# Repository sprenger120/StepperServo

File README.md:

# Stepper Servo

Steering the car with the might of stepper motors

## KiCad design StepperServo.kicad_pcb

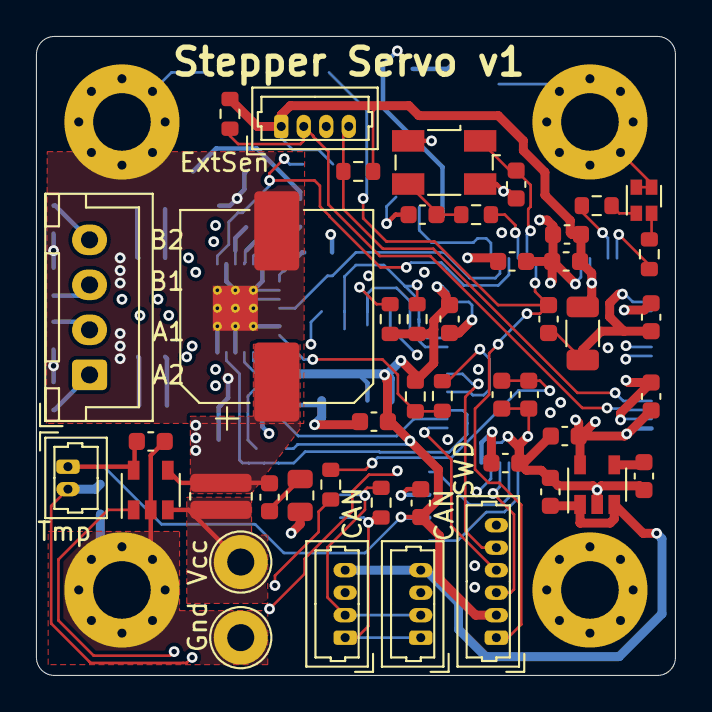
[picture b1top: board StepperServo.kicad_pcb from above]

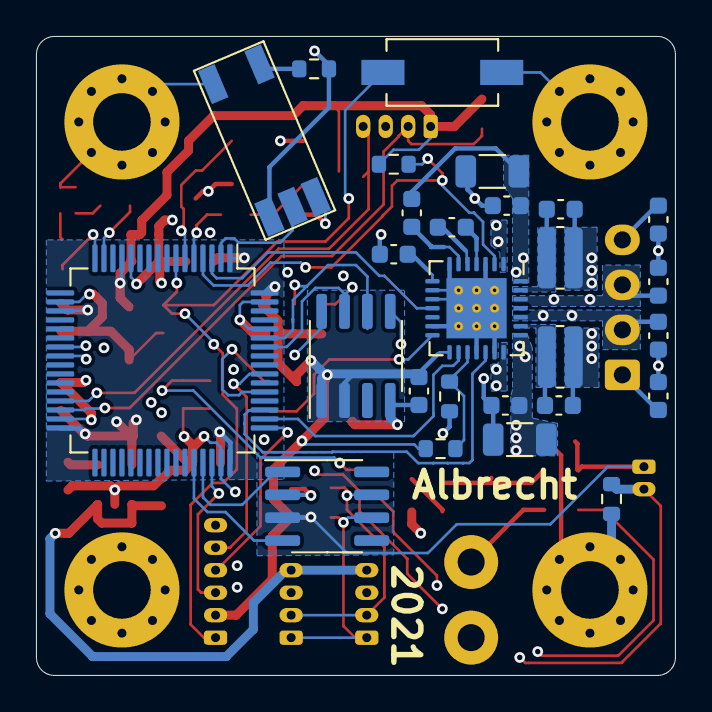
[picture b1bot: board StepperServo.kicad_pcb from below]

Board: 4 copper layers, 35.5 x 35.5 mm, 77 parts (27 on the bottom side), 48 nets.

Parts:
C1, C7, C8, C12, C13, C14, C18, C21, C23, C24, C25, C26, C27, C35, C39, C40, C41: 100nF 35V; C_0603_1608Metric
C2, C4, C9, C28: 1uF 35V; C_0603_1608Metric
C3, C17, C19, C20, C22: 470pF 100V; C_0603_1608Metric
C5, C10, C11: 10uF 35V; C_1206_3216Metric
C6: 330uF 35V; CP_Elec_10x10.5
C15: 22nF 50V; C_0603_1608Metric
C16: 2.2uF 16V; C_0603_1608Metric
C30: 10nF; C_0603_1608Metric
C33, C34: 15pF; C_0603_1608Metric
D1: LTST-C195TGKRKT; LED_LiteOn_LTST-C195TGKRKT
H1, H2, H3, H4: MountingHole_Pad; MountingHole_3.2mm_M3_Pad_Via
J1, J2: Conn_01x01_Female; TestPoint_Loop_D2.54mm_Drill1.5mm_Beaded
J3: Conn_01x04_Male; JST_XH_B4B-XH-A_1x04_P2.50mm_Vertical
J4: I2C_External; Molex_PicoBlade_53047-0410_1x04_P1.25mm_Vertical
J6: Conn_TempMotor; Molex_PicoBlade_53047-0210_1x02_P1.25mm_Vertical
J_CAN1, J_CAN2: Molex PicoBlade 4Pin; Molex_PicoBlade_53047-0410_1x04_P1.25mm_Vertical
J_SWD1: Molex PicoBlade 6Pin; Molex_PicoBlade_53047-0610_1x06_P1.25mm_Vertical
OPT1: SX3340; Omron_SX_3340
R1: 0.11; R_0612_1632Metric
R2: 120; R_0603_1608Metric
R3: 1.1R 0.5W; R_0805_2012Metric
R4: 1k; R_0603_1608Metric
R5, R7: 22k; R_0603_1608Metric
R6: 4.7k; R_0603_1608Metric
R9, R10: 270m; R_0612_1632Metric
R11, R20, R23: 10k; R_0603_1608Metric
R12, R13: 4k7; R_0603_1608Metric
R14, R15: 2k; R_0603_1608Metric
R16, R22: 220; R_0603_1608Metric
R19: 100; R_0603_1608Metric
R21: 380; R_0603_1608Metric
SW4: SW_Reset; SW_SPST_PTS636_SM25F
U1: TC1185; SOT-23-5
U2: SN65HVD232; SOIC-8_3.9x4.9mm_P1.27mm
U3: TMC2209-LA; QFN-28-1EP_5x5mm_P0.5mm_EP3.35x3.35mm_ThermalVias
U5: STM32F103RETx; LQFP-64_10x10mm_P0.5mm
U6: AS5600; SOIC-8_3.9x4.9mm_P1.27mm
U7: INA180A1; SOT-23-5
Y1: ABM3B-16MHz; Crystal_SMD_Abracon_ABM3B-4Pin_5.0x3.2mm

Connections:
+3V3: C1.1, C4.1, C5.2, C8.1, C23.2, C24.2, C25.2, C26.2, C27.2, C28.1, C30.1, C39.1, C41.1, J4.1, J6.1, J_SWD1.2, R5.1, R6.2, R7.1, R12.2, R13.1, R14.1, R15.1, U1.5, U2.3, U3.15, U5.1, U5.13, U5.19, U5.32, U5.48, U5.64, U6.1, U6.2, U7.5
+5V: C2.1, J_CAN1.4, J_CAN2.4, OPT1.3, R16.1, U1.1, U1.3
/CAN_RX: U2.4, U5.44
/CAN_TX: U2.1, U5.45
/MCU/I2C1_SCL: R15.2, U5.58, U6.7
/MCU/I2C1_SDA: R14.2, U5.59, U6.6
/MCU/I2C2_SCL: J4.4, R12.1, U5.29
/MCU/I2C2_SDA: J4.2, R13.2, U5.30
/MCU/LED_GREEN: R22.1, U5.15
/MCU/LED_RED: R21.1, U5.16
/MCU/SWCLK: J_SWD1.4, U5.49
/MCU/SWDIO: J_SWD1.3, U5.46
/MCU/SWO: J_SWD1.5, U5.55
/MCU/Stepper_UART: R4.2, U5.53
/MCU/endstopRight: OPT1.4, U5.2
/MCU/tempMotor: J6.2, R20.1, U5.24
/MCU/~RST: C35.1, J_SWD1.1, SW4.2, U5.7
/StepperDriver/Diag: U3.11, U5.3
/StepperDriver/Direction: U3.19, U5.51
/StepperDriver/Step: U3.16, U5.50
/StepperDriver/Vref: R7.2, R11.1, U3.17
/StepperDriver/chargePumpIn: C15.1, U3.5
/StepperDriver/chargePumpOut: C15.2, U3.4
/StepperDriver/chargePumpVoltage: C12.2, U3.6
/StepperDriver/coilA_1: C19.1, J3.2, U3.24
/StepperDriver/coilA_2: C17.1, J3.1, U3.21
/StepperDriver/coilB_1: C20.1, J3.3, U3.26
/StepperDriver/coilB_2: C22.1, J3.4, U3.1
/StepperDriver/internal5VReg: C16.1, U3.8
/StepperDriver/senseCoilA: C18.1, R9.2, U3.23
/StepperDriver/senseCoilB: C21.1, R10.2, U3.27
/StepperDriver/~EN: R5.2, U3.2, U5.4
/inputCurrent: C7.1, C40.1, R23.1, U5.23
GND: C1.2, C2.2, C3.2, C4.2, C5.1, C6.2, C7.2, C8.2, C10.2, C11.2, C13.2, C14.2, C16.2, C17.2, C18.2, C19.2, C20.2, C21.2, C22.2, C23.1, C24.1, C25.1, C26.1, C27.1, C28.2, C30.2, C33.1, C34.1, C35.2, C39.2, C40.2, C41.2, D1.3, D1.4, H1.1, H2.1, H3.1, H4.1, J2.1, J4.3, J_CAN1.3, J_CAN2.3, J_SWD1.6, OPT1.2, OPT1.5, R3.2, R9.1, R10.1, R11.2, R20.2, SW4.1, U1.2, U2.2, U3.3, U3.7, U3.9, U3.10, U3.13, U3.18, U3.20, U3.29, U5.12, U5.18, U5.31, U5.47, U5.60, U5.63, U6.4, U6.5, U6.8, U7.2, Y1.2, Y1.4
unnamed: C3.1, U1.4
unnamed: C9.2, R3.1
unnamed: C33.2, R19.2, Y1.3
unnamed: C34.2, U5.6, Y1.1
unnamed: D1.1, R22.2
unnamed: D1.2, R21.2
unnamed: J1.1, R1.2, U7.3
unnamed: J_CAN1.1, J_CAN2.1, R2.2, U2.6
unnamed: J_CAN1.2, J_CAN2.2, R2.1, U2.7
unnamed: OPT1.1, R16.2
unnamed: R4.1, R6.1, U3.14
unnamed: R19.1, U5.5
unnamed: R23.2, U7.1
VCC: C6.1, C9.1, C10.1, C11.1, C12.1, C13.1, C14.1, R1.1, U3.22, U3.28, U7.4

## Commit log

2020-11-22 updated standardcontent
2020-11-22 wip schematic
2021-05-03 Specified dual led resistors Consolidated all grounds to just gnd Consolidated all 3.3 rails to just 3.3V Removed right endstop Removed right wheel angle, servo angle calibration button
2021-05-03 Renamed ui buttons for better clarity
2021-05-03 wip layout
2021-05-04 Finished v1 layout Added pictures to readme
2021-05-05 fixed wrong shunt ohm value
2022-01-12 exported step file exported production files fixed omron photo interruper 3d model
2022-01-12 Create LICENSE
